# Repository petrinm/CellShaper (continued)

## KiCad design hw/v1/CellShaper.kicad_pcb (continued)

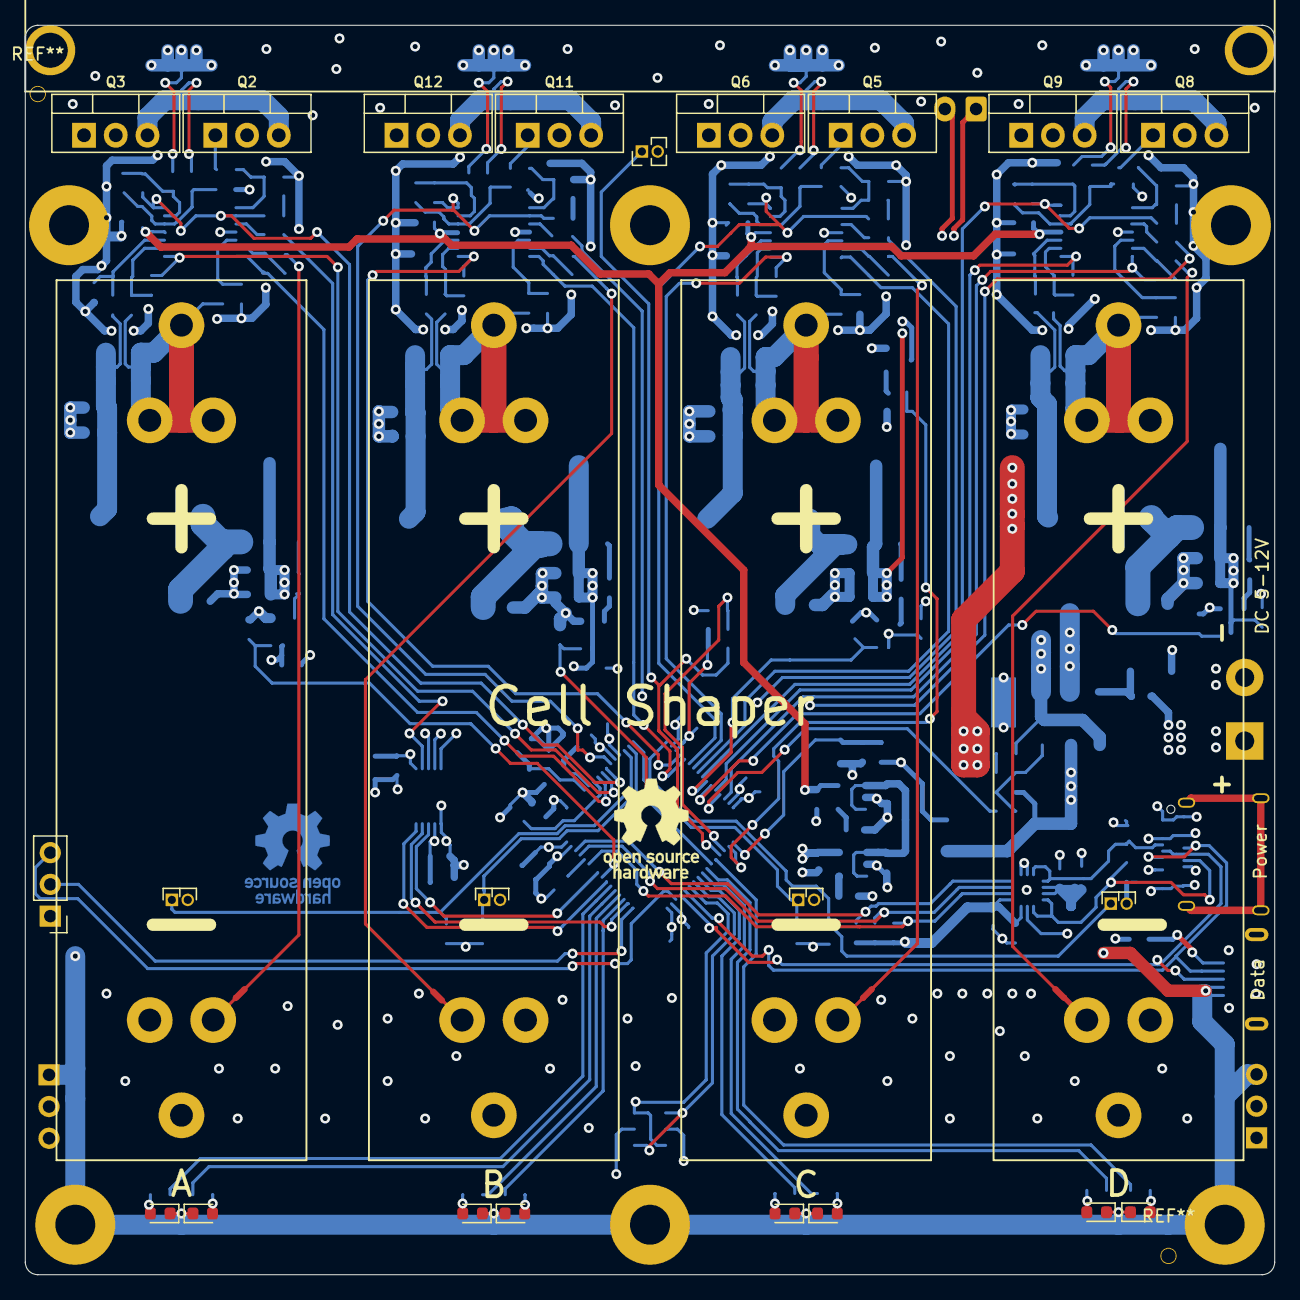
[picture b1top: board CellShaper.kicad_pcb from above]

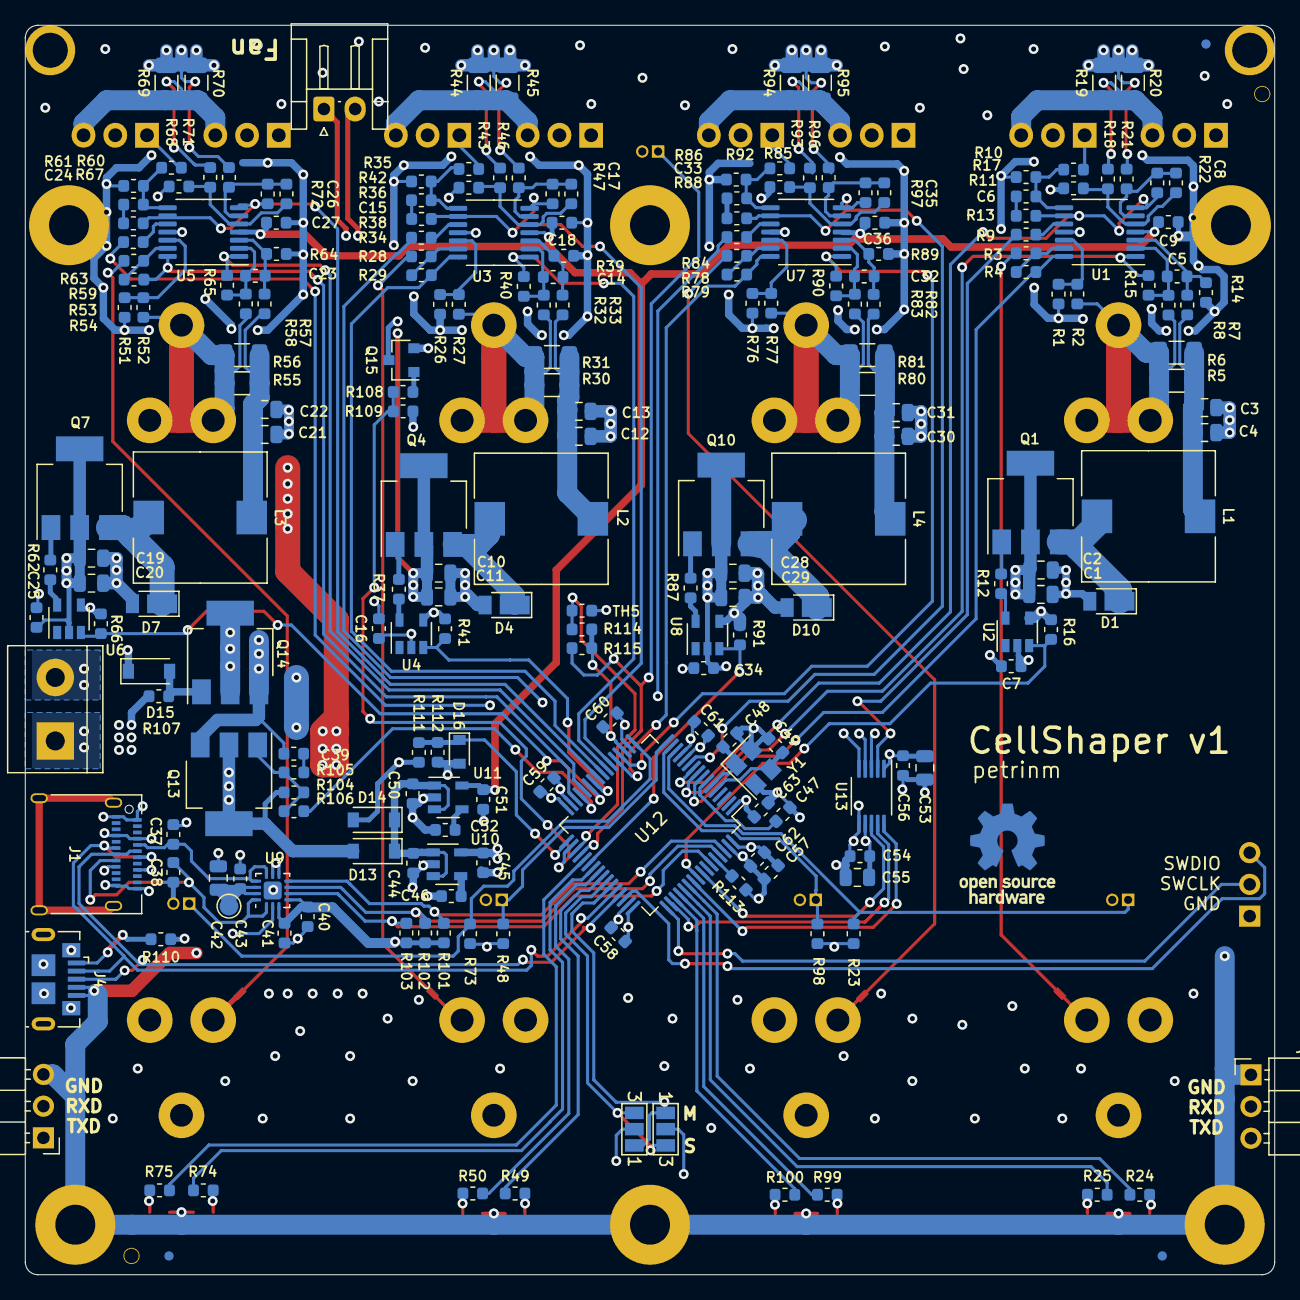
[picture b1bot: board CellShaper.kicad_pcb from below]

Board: 4 copper layers, 100.0 x 100.0 mm, 262 parts (224 on the bottom side), 150 nets.

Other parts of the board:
L2, L3, L4: 100u; L_Wuerth_HCM-1052
LOGO1#2: Logo_Open_Hardware_Small; OSHW-Logo_7.5x8mm_Copper

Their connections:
unnamed 78: L2.2; also elsewhere on the board
unnamed 85: L3.2; also elsewhere on the board
unnamed 92: L4.2; also elsewhere on the board
unnamed 106: L2.1; also elsewhere on the board
unnamed 109: L3.1; also elsewhere on the board
unnamed 112: L4.1; also elsewhere on the board

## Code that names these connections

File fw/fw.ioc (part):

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Mcu.Name=STM32F303R(B-C)Tx
Mcu.Package=LQFP64
Mcu.UserName=STM32F303RBTx
PA0.Mode=IN1-Single-Ended
PA0.Signal=ADC1_IN1
PA1.Mode=IN2-Single-Ended
PA1.Signal=ADC1_IN2
PA10.GPIOParameters=GPIO_ModeDefaultPP,GPIO_PuPd,GPIO_Label
PA10.GPIO_Label=RXD
PA10.GPIO_ModeDefaultPP=GPIO_MODE_AF_OD
PA10.GPIO_PuPd=GPIO_PULLUP
PA10.Mode=Asynchronous
PA10.Signal=USART1_RX
PA11.Mode=Device
PA11.Signal=USB_DM
PA12.Mode=Device
PA12.Signal=USB_DP
PA13.Mode=Serial_Wire
PA13.Signal=SYS_JTMS-SWDIO
PA14.Mode=Serial_Wire
PA14.Signal=SYS_JTCK-SWCLK
PA15.Mode=NSS_Signal_Hard_Output
PA15.Signal=SPI1_NSS
PA2.Mode=IN3-Single-Ended
PA2.Signal=ADC1_IN3
PA3.Mode=IN4-Single-Ended
PA3.Signal=ADC1_IN4
PA4.Mode=IN1-Single-Ended
PA4.Signal=ADC2_IN1
PA5.Mode=IN2-Single-Ended
PA5.Signal=ADC2_IN2
PA6.Mode=IN3-Single-Ended
PA6.Signal=ADC2_IN3
PA7.Mode=IN4-Single-Ended
PA7.Signal=ADC2_IN4
PA8.Signal=GPIO_Output
PA9.GPIOParameters=GPIO_ModeDefaultPP,GPIO_PuPd,GPIO_Label
PA9.GPIO_Label=TXD
PA9.GPIO_ModeDefaultPP=GPIO_MODE_AF_OD
PA9.GPIO_PuPd=GPIO_PULLUP
PA9.Mode=Asynchronous
PA9.Signal=USART1_TX
PB0.Mode=IN12-Single-Ended
PB0.Signal=ADC3_IN12
PB1.Signal=S_TIM3_CH4
PB13.Mode=IN5-Single-Ended
PB13.Signal=ADC3_IN5
PB14.Signal=GPIO_Output
PB15.Signal=GPIO_Output
PB2.Mode=IN12-Single-Ended
PB2.Signal=ADC2_IN12
PB3.Mode=TX_Only_Simplex_Unidirect_Master
PB3.Signal=SPI1_SCK
PB4.Signal=GPXTI4
PB5.Mode=TX_Only_Simplex_Unidirect_Master
PB5.Signal=SPI1_MOSI
PB6.Mode=I2C
PB6.Signal=I2C1_SCL
PB7.Mode=I2C
PB7.Signal=I2C1_SDA
PC0.Signal=ADCx_IN6
PC1.Signal=ADCx_IN7
PC10.Signal=GPIO_Output
PC11.Signal=GPIO_Output
PC12.Signal=GPIO_Output
PC2.Signal=ADCx_IN8
PC3.Signal=ADCx_IN9
PC4.Mode=IN5-Single-Ended
PC4.Signal=ADC2_IN5
PC5.Mode=IN11-Single-Ended
PC5.Signal=ADC2_IN11
PC6.Signal=S_TIM3_CH1
PC7.Signal=S_TIM3_CH2
PC8.Signal=S_TIM3_CH3
PC9.Signal=GPIO_Output
PD2.Signal=GPIO_Output
PF0-OSC_IN.Mode=HSE-External-Oscillator
PF0-OSC_IN.Signal=RCC_OSC_IN
PF1-OSC_OUT.Mode=HSE-External-Oscillator
PF1-OSC_OUT.Signal=RCC_OSC_OUT
PF4.Mode=IN5-Single-Ended
PF4.Signal=ADC1_IN5
RCC.HSEPLLFreq_Value=8000000
RCC.HSE_VALUE=8000000
RCC.SYSCLKFreq_VALUE=48000000
RCC.SYSCLKSourceVirtual=RCC_SYSCLKSOURCE_PLLCLK
board=custom

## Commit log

2020-05-08 First draft of the schema and pcb
2020-07-06 Add CubeMX design file
2020-07-06 Progress with the schema and PCB....
2020-07-09 Progress...
2020-07-10 Soon...
2020-07-11 Soooooon...
2020-07-15 Layout done and MCU pins rearranged
